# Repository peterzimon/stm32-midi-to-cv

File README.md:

# STM32 MIDI to CV converter

Polyphonic MIDI to CV converter using STM32F103 (blue pill)

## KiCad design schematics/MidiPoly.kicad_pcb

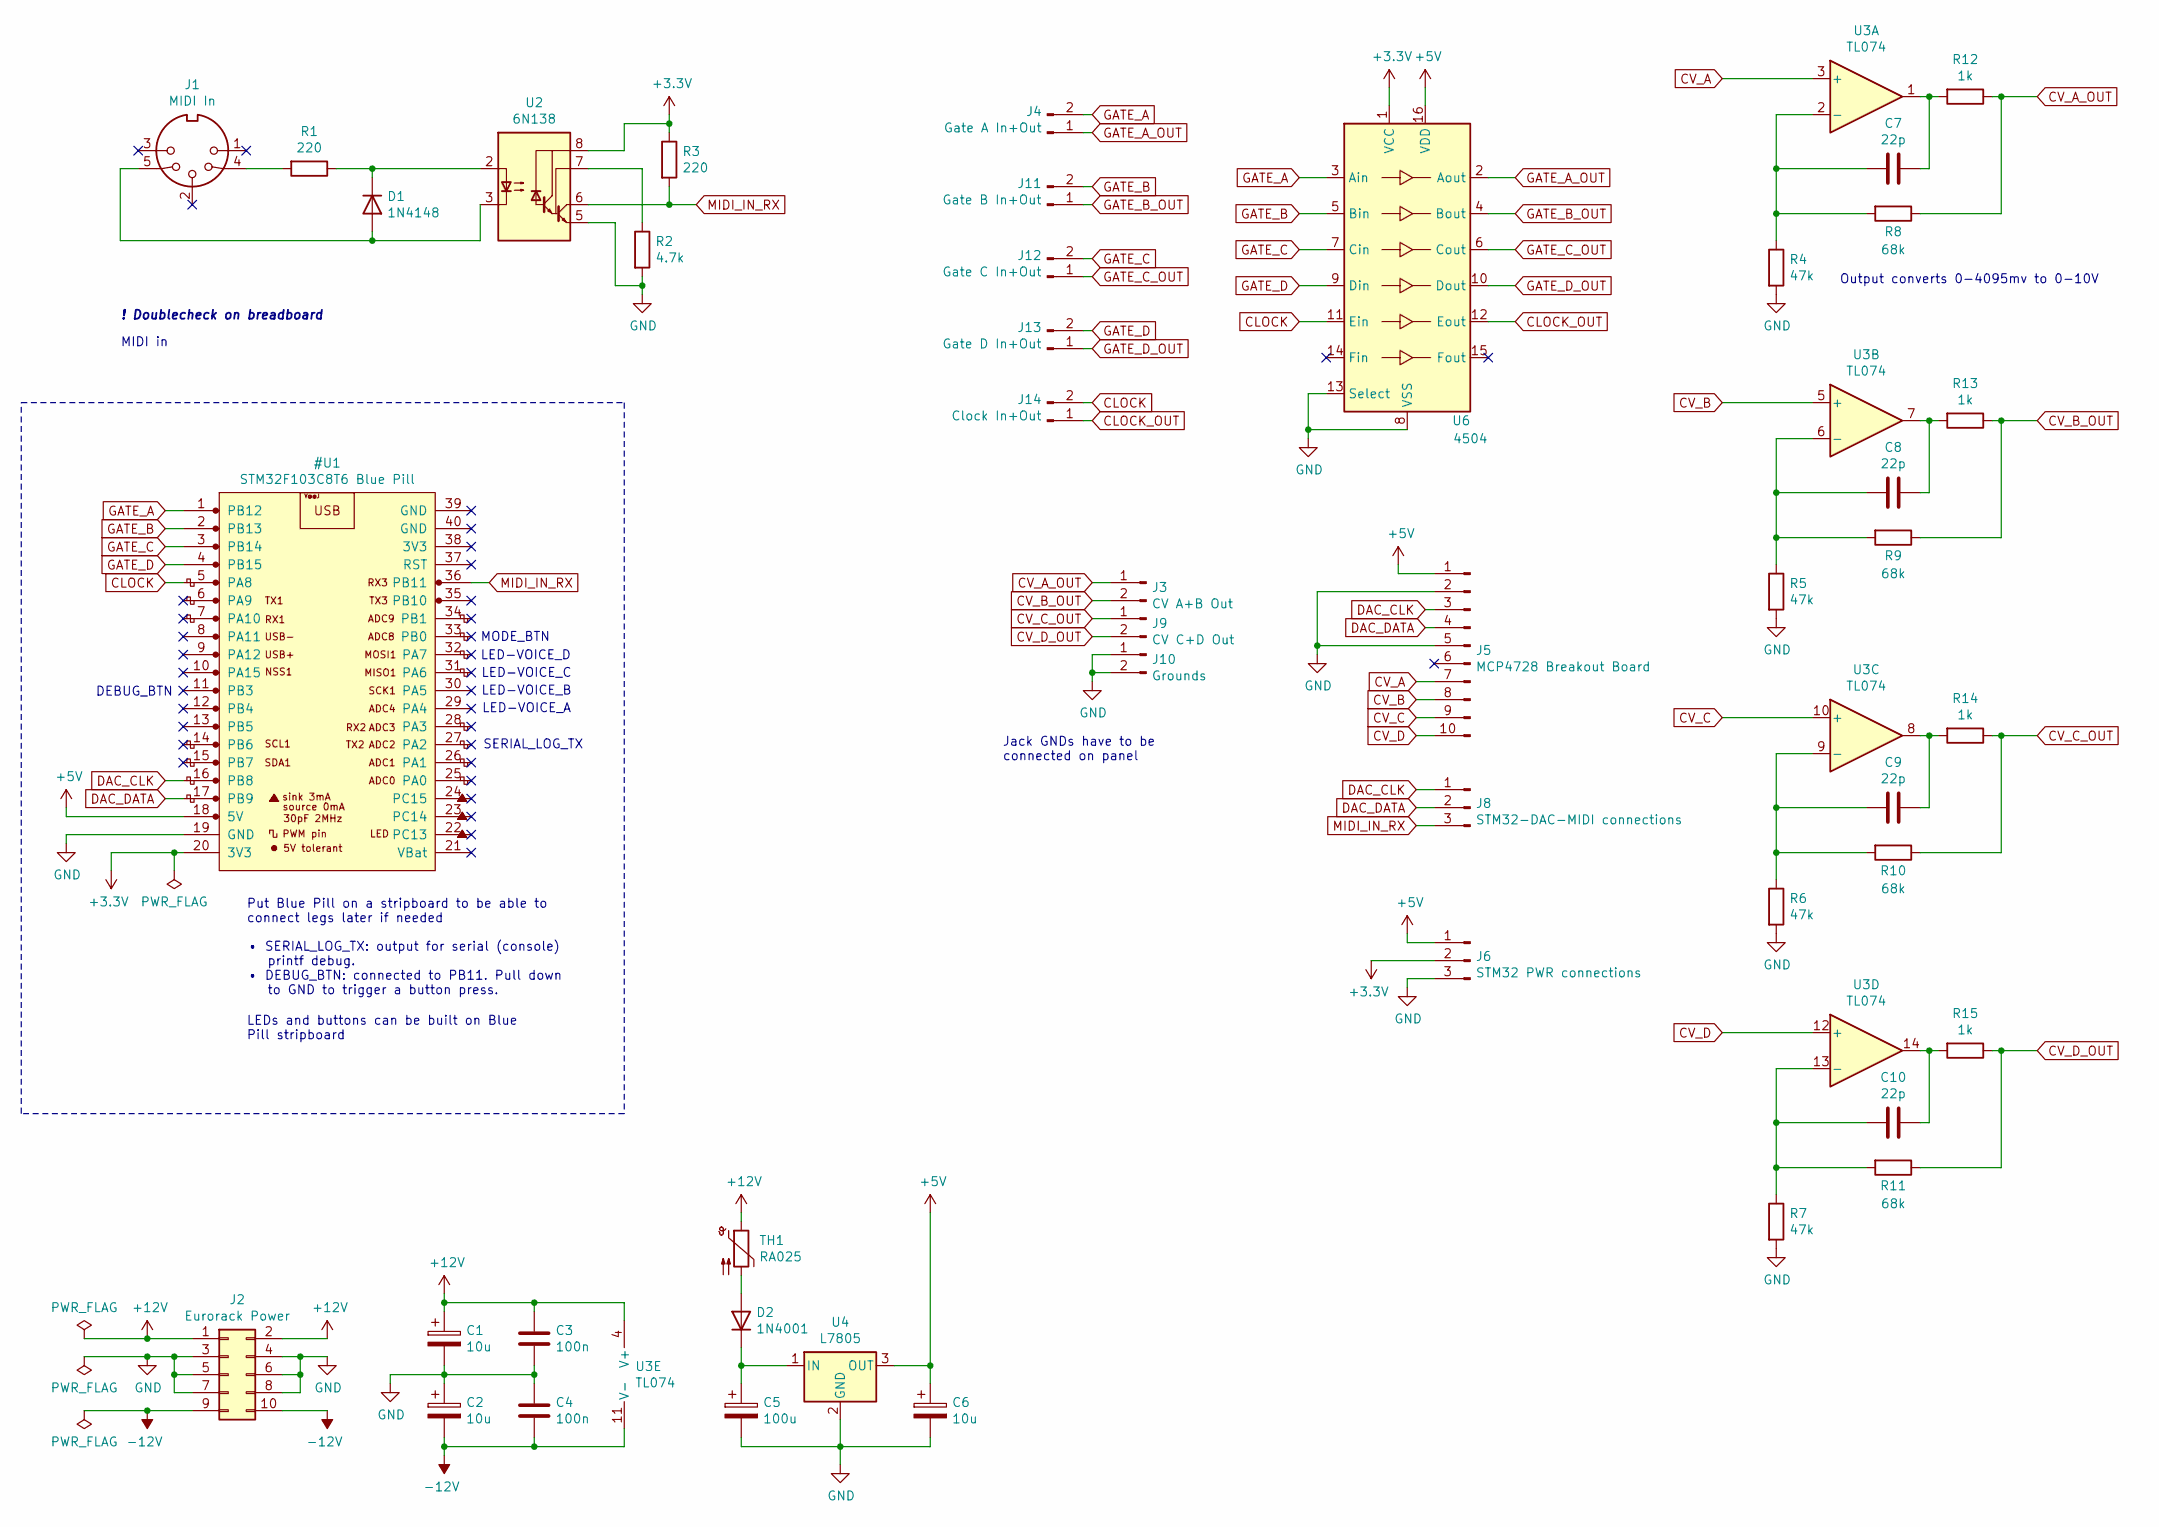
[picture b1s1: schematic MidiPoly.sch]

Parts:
C1, C2, C6: 10u; CP_Radial_D5.0mm_P2.50mm
C3, C4: 100n; C_Disc_D5.0mm_W2.5mm_P2.50mm
C5: 100u; CP_Radial_D5.0mm_P2.50mm
C7, C8, C9, C10: 22p; C_Disc_D5.0mm_W2.5mm_P2.50mm
D1: 1N4148; D_Axial
D2: 1N4001; D_Axial
J1: MIDI In; MIDI_Input
J2: Eurorack Power; Eurorack_Power_Supply
J3: CV A+B Out; PinOut_01x02
J4: Gate A In+Out; PinOut_01x02
J5: MCP4728 Breakout Board; PinOut_01x10
J6: STM32 PWR connections; PinOut_01x03
J8: STM32-DAC-MIDI connections; PinOut_01x03
J9: CV C+D Out; PinOut_01x02
J10: Grounds; PinOut_01x02
J11: Gate B In+Out; PinOut_01x02
J12: Gate C In+Out; PinOut_01x02
J13: Gate D In+Out; PinOut_01x02
J14: Clock In+Out; PinOut_01x02
R1, R3: 220; R_Axial_Vertical
R2: 4.7k; R_Axial_Vertical
R4, R5, R6, R7: 47k; R_Axial_Vertical
R8, R9, R10, R11: 68k; R_Axial_Vertical
R12, R13, R14, R15: 1k; R_Axial_Vertical
TH1: RA025; R_Axial_DIN0207_L6.3mm_D2.5mm_P7.62mm_Horizontal
U2: 6N138; DIP-8_W7.62mm
U3: TL074; DIP-14_W7.62mm
U4: L7805; TO-220-3_Vertical
U6: 4504; DIP-16_W7.62mm

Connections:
+12V: C1.1, C3.1, J2.1, J2.2, TH1.1, U3.4 (V+)
-12V: C2.2, C4.2, J2.9, J2.10, U3.11 (V-)
CLOCK_OUT: J14.1, U6.12 (Eout)
CV_A: J5.7, U3.3 (+)
CV_A_OUT: J3.1, R8.1, R12.1
CV_B: J5.8, U3.5 (+)
CV_B_OUT: J3.2, R9.1, R13.1
CV_C: J5.9, U3.10 (+)
CV_C_OUT: J9.1, R10.1, R14.1
CV_D: J5.10, U3.12 (+)
CV_D_OUT: J9.2, R11.1, R15.1
GATE_A_OUT: J4.1, U6.2 (Aout)
GATE_B_OUT: J11.1, U6.4 (Bout)
GATE_C_OUT: J12.1, U6.6 (Cout)
GATE_D_OUT: J13.1, U6.10 (Dout)
unnamed: C5.1, D2.1 (K), U4.1 (IN)
unnamed: C7.1, R12.2, U3.1
unnamed: C7.2, R4.1, R8.2, U3.2 (-)
unnamed: C8.1, R13.2, U3.7
unnamed: C8.2, R5.1, R9.2, U3.6 (-)
unnamed: C9.1, R14.2, U3.8
unnamed: C9.2, R6.1, R10.2, U3.9 (-)
unnamed: C10.1, R15.2, U3.14
unnamed: C10.2, R7.1, R11.2, U3.13 (-)
unnamed: D1.1 (K), R1.1, U2.2 (C1)
unnamed: D1.2 (A), J1.5, U2.3 (C2)
unnamed: D2.2 (A), TH1.2
unnamed: J1.4, R1.2
unnamed: R2.1, U2.7 (VO1)

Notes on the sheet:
MIDI in
! Doublecheck on breadboard
Output converts 0-4095mv to 0-10V
• SERIAL_LOG_TX: output for serial (console) printf debug. • DEBUG_BTN: connected to PB11. Pull down to GND to trigger a button press.
Put Blue Pill on a stripboard to be able to connect legs later if needed
SERIAL_LOG_TX
DEBUG_BTN
LEDs and buttons can be built on Blue Pill stripboard
Jack GNDs have to be connected on panel
LED-VOICE_A
LED-VOICE_B
LED-VOICE_C
LED-VOICE_D
MODE_BTN

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
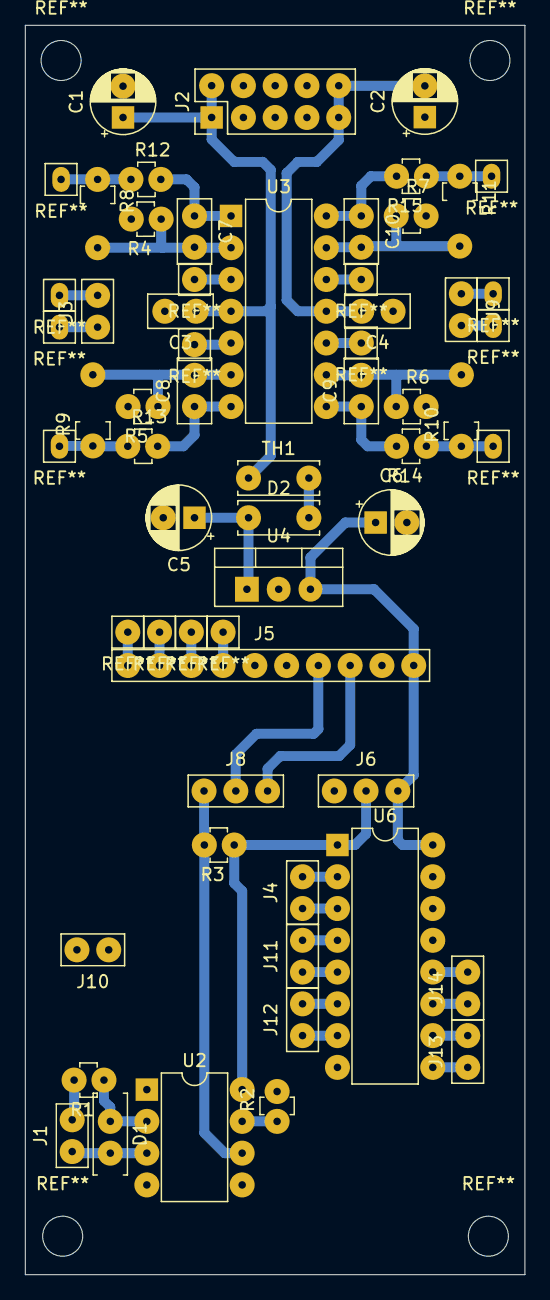
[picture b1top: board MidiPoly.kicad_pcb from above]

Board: 2 copper layers, 39.9 x 99.9 mm, 45 parts (0 on the bottom side), 40 nets.

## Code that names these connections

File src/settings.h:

#ifndef SETTINGS_H
#define SETTINGS_H

// #define SERIAL_DEBUG // Comment/uncomment to turn off/on serial debugging
#define VOICES 4

// Midi note mapping to CV
#define LOWEST_MIDI_NOTE 0x00
#define OCTAVES 10
#define MAX_NOTE_VOLTAGE 4095   // Max voltage to map the midi notes to. 
                                // Read comment Note in cvgate.cpp::cvForNote()

// Non-note CV
#define MAX_CV_VOLTAGE 2047 // Since the hardware amplifies the output by A = 1 + (69/47), 
                            // a max of 2047 will result in cca. +5V

// Buttons
#define MODE_BUTTON_PORT        GPIOB
#define MODE_BUTTON_PIN         GPIO_PIN_0
#define DEBUG_BUTTON_PORT       GPIOB
#define DEBUG_BUTTON_PIN        GPIO_PIN_3

// LEDs
#define VOICE_LED_PORT          GPIOA
#define VOICE_A_LED_PIN         GPIO_PIN_4
#define VOICE_B_LED_PIN         GPIO_PIN_5
#define VOICE_C_LED_PIN         GPIO_PIN_6
#define VOICE_D_LED_PIN         GPIO_PIN_7
#define BUILT_IN_LED_PORT       GPIOC
#define BUILT_IN_LED_PIN        GPIO_PIN_13

// Gate GPIO pins
#define GATE_PORT               GPIOB
#define GATE_A                  GPIO_PIN_12
#define GATE_B                  GPIO_PIN_13
#define GATE_C                  GPIO_PIN_14
#define GATE_D                  GPIO_PIN_15

// UI constants
#define BLINK_DURATION          100
#define BUTTON_DEBOUNCE         250

enum device_mode {
    MONO,
    CIRCULAR,
    UNISON,
    POLY,
    BCH,
    CHL,
    QUAD
};

struct Settings
{
    device_mode mode;
    bool modeDirty; // Used for flagging if settings been updated
};

extern Settings settings;

#endif

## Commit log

2021-04-16 Updated comments
2021-04-16 Cleanup
2021-04-17 Added basic monophonic handler
2021-04-17 Added basic polyphony handling
2021-04-18 Updated last note prio logic
2021-04-18 Separated CVGate handling
2021-04-18 Updated mono mode
2021-04-18 Updated velocity in mono mode
2021-04-18 Basic DAC driver (untested)
2021-04-18 Added DAC write
2021-04-19 A couple of things
    - moved all HAL msp callbacks to system.cpp
    - added gate handler
    - added more comments
    - general cleanup
    BTW, the thing works now!
2021-04-21 Removed delay (WORKS 0.1)
2021-04-21 Adjusted voltage calculation to 10 octaves (0-10V)
2021-04-21 Updated CV bug
2021-04-21 Added naive calibration
2021-04-21 Added naive calibration per channel
2021-04-21 Added unison mode
2021-04-21 Refined unison
2021-04-24 Added circular mode
2021-04-24 Merged all mono modes
2021-04-24 Added note history
2021-04-24 Added note + chord modes
2021-04-25 Added proper calibration
2021-04-25 Added calibration comments
2021-04-28 Added basic LED handling
2021-04-28 Updated leds
2021-04-29 Added blinking
2021-04-29 Added LED lightshow and mode change
2021-05-03 Added latch to mono mode
2021-05-03 Added latch to poly modes
2021-05-03 Added latch to quad mode
2021-05-03 Added reset on mode change
2021-05-04 Fixed pitch bend bug
2021-05-04 Fixed hard reset bug when mode changed
2022-10-25 Added schematics
2022-10-25 Added gitignore
